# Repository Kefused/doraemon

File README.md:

doraemon
========

Doreamon Project

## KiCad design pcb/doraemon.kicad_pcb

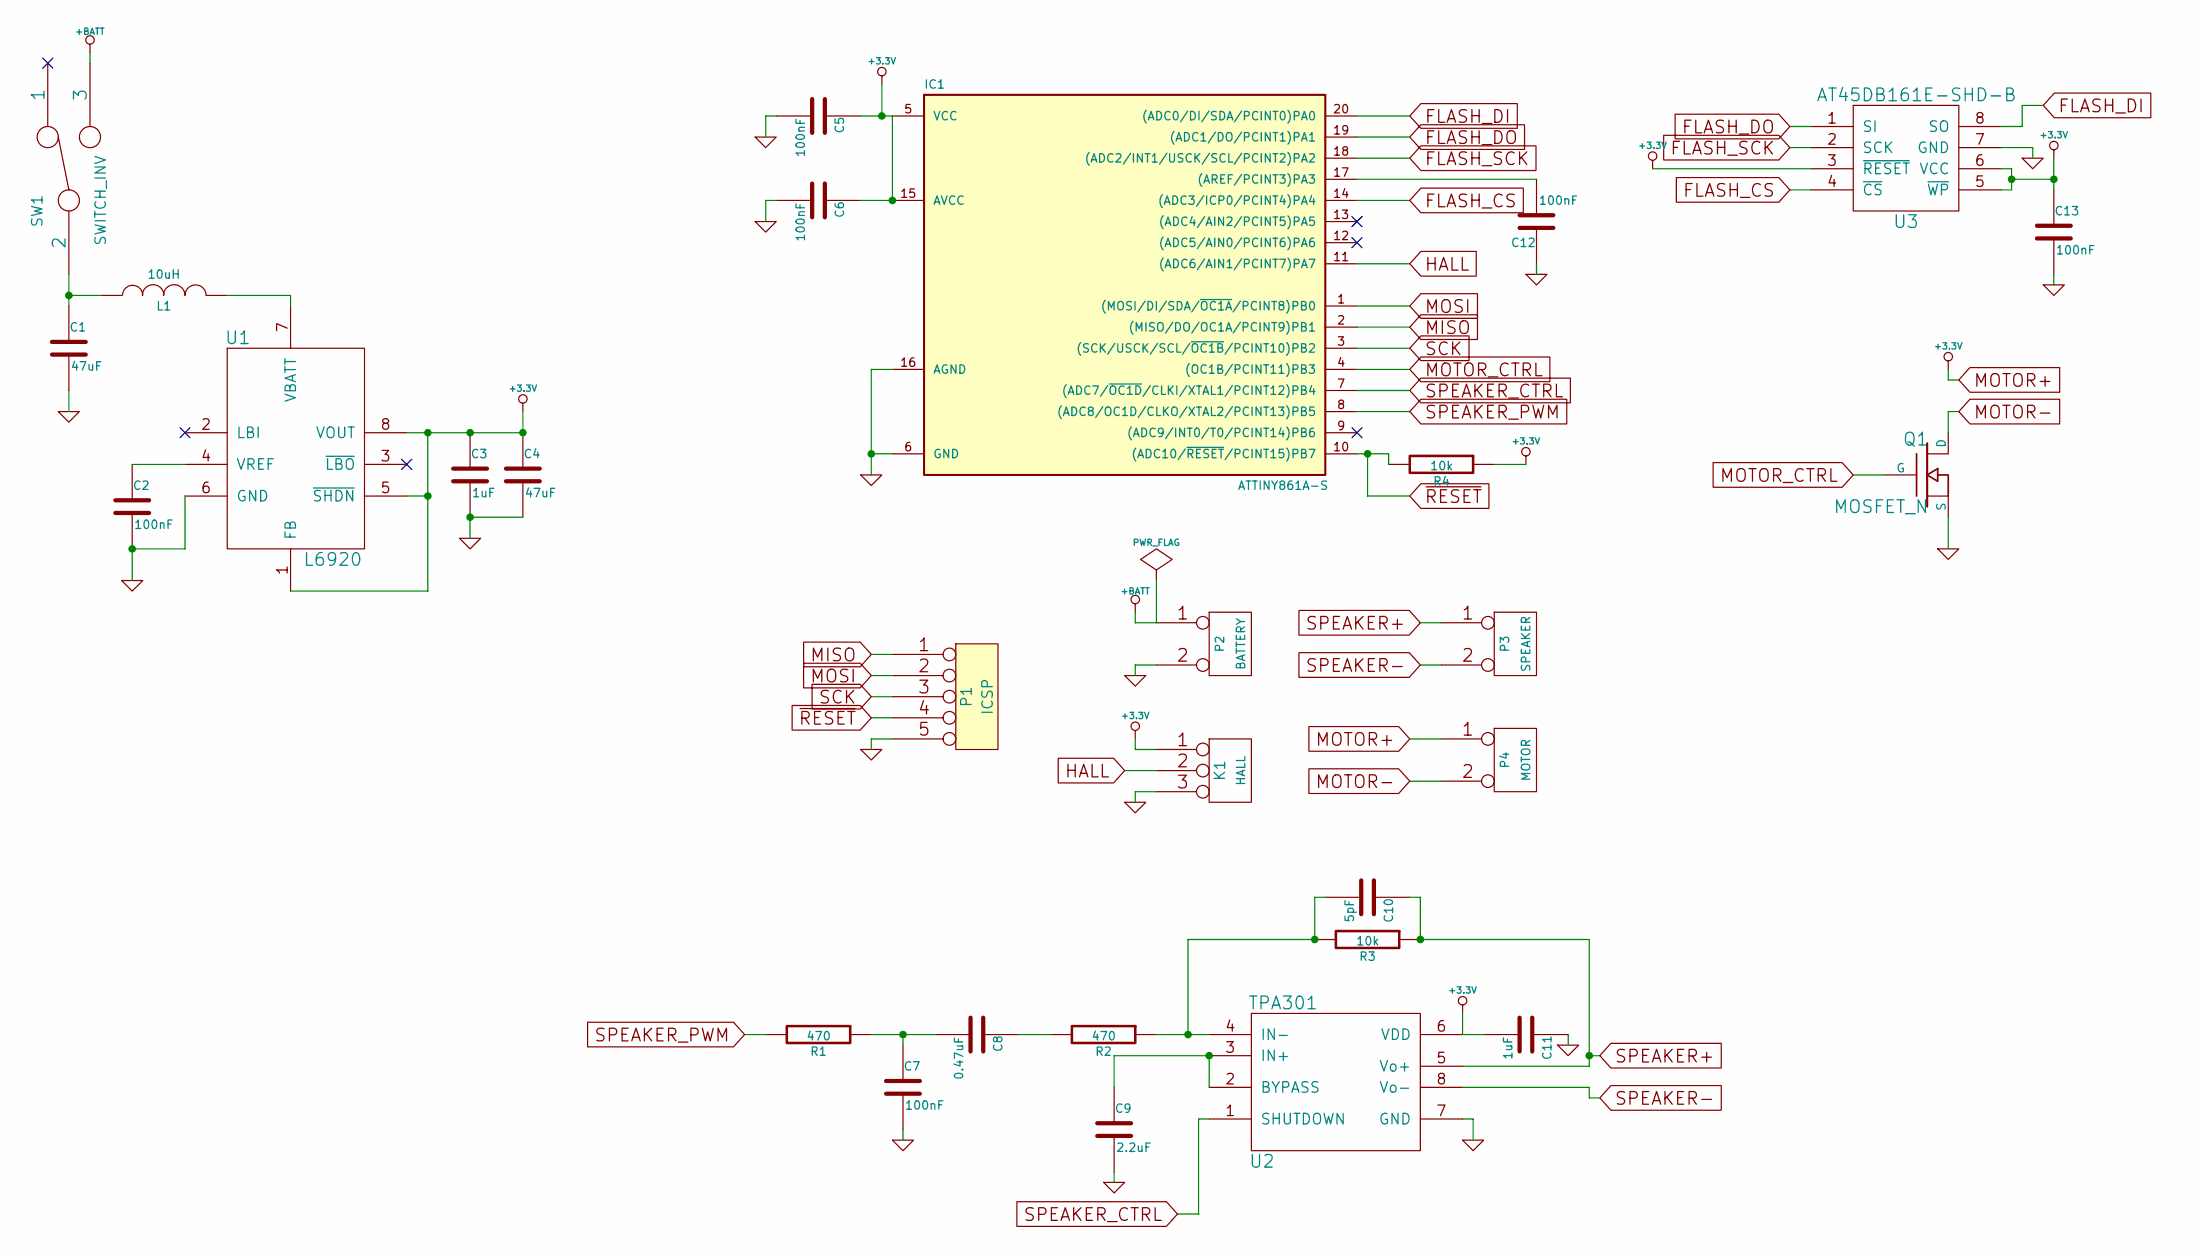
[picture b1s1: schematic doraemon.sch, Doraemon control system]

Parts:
C1, C4: 47uF; SM0805; Farnell 1886100
C2, C5, C6, C7, C12, C13: 100nF; SM0805; Farnell 2332715
C3, C11: 1uF; SM0805; Farnell 1833845
C8: 0.47uF; SM0805; Farnell 1867963
C9: 2.2uF; SM0805; Farnell 1288262
C10: 5pF; SM0805; Farnell 2332708
IC1: ATTINY861A-S; AB2_SO20_W; Farnell 1841628
K1: HALL; 3wire; Farnell 1225624
L1: 10uH; DO1608C; Farnell 2287199
P1: ICSP; icsp
P2: BATTERY; 2wire
P3: SPEAKER; 2wire; Farnell 2357168
P4: MOTOR; 2wire
Q1: MOSFET_N; SOT23; Farnell 9512608
R1: 470; SM0805; Farnell 2341030
R2: 470; SM0805; Farnell 2141884
R3, R4: 10k; SM0805; Farnell 1612522
SW1: SWITCH_INV; SWITCH; Farnell 1123872
U1: L6920; AB2_TSSOP08; Farnell 1077152
U2: TPA301
U3: AT45DB161E-SHD-B; SO8E; Farnell 2136670

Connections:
+BATT: P2.1, SW1.3
FLASH_CS: IC1.14 ((ADC3/ICP0/PCINT4)PA4), U3.4 (~CS)
FLASH_DI: IC1.20 ((ADC0/DI/SDA/PCINT0)PA0), U3.8 (SO)
FLASH_DO: IC1.19 ((ADC1/DO/PCINT1)PA1), U3.1 (SI)
FLASH_SCK: IC1.18 ((ADC2/INT1/USCK/SCL/PCINT2)PA2), U3.2 (SCK)
GND: C1.2, C2.2, C3.2, C4.2, C5.2, C6.2, C7.2, C9.2, C11.1, C12.1, C13.2, IC1.6 (GND), IC1.16 (AGND), K1.3, P1.5, P2.2 (PM), Q1.S, U1.6 (GND), U2.7 (GND), U3.7 (GND)
HALL: IC1.11 ((ADC6/AIN1/PCINT7)PA7), K1.2 (PM)
MISO: IC1.2 ((MISO/DO/OC1A/PCINT9)PB1), P1.1
MOSI: IC1.1 ((MOSI/DI/SDA/~OC1A~/PCINT8)PB0), P1.2
MOTOR+: C3.1, C4.1, C5.1, C6.1, C11.2, C13.1, IC1.5 (VCC), IC1.15 (AVCC), K1.1, P4.1, R4.1, U1.1 (FB), U1.5 (~SHDN), U1.8 (VOUT), U2.6 (VDD), U3.3 (~RESET), U3.5 (~WP), U3.6 (VCC)
MOTOR-: P4.2 (PM), Q1.D
MOTOR_CTRL: IC1.4 ((OC1B/PCINT11)PB3), Q1.G
unnamed: C1.1, L1.1, SW1.2
unnamed: C2.1, U1.4 (VREF)
unnamed: C7.1, C8.2, R1.1
unnamed: C8.1, R2.2
unnamed: C9.1, U2.2 (BYPASS), U2.3 (IN+)
unnamed: C10.2, R2.1, R3.2, U2.4 (IN-)
unnamed: C12.2, IC1.17 ((AREF/PCINT3)PA3)
unnamed: L1.2, U1.7 (VBATT)
SCK: IC1.3 ((SCK/USCK/SCL/~OC1B~/PCINT10)PB2), P1.3
SPEAKER+: C10.1, P3.1, R3.1, U2.5 (Vo+)
SPEAKER-: P3.2 (PM), U2.8 (Vo-)
SPEAKER_CTRL: IC1.7 ((ADC7/~OC1D~/CLKI/XTAL1/PCINT12)PB4), U2.1 (SHUTDOWN)
SPEAKER_PWM: IC1.8 ((ADC8/OC1D/CLKO/XTAL2/PCINT13)PB5), R1.2
~RESET: IC1.10 ((ADC10/~RESET~/PCINT15)PB7), P1.4, R4.2

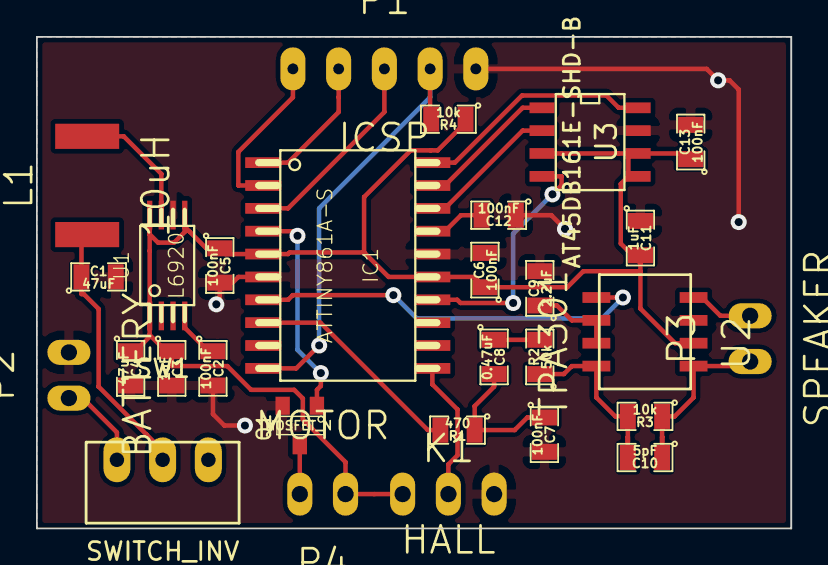
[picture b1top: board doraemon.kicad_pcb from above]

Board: 2 copper layers, 41.9 x 27.3 mm, 29 parts (0 on the bottom side), 26 nets.

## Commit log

2015-01-14 Adding PCB files
